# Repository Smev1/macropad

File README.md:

This is my Hack Club Hack Pad!

I am making this to learn about how to use KiCAD!

PCB Schematic:

CAD Assembled:

CAD Parts:

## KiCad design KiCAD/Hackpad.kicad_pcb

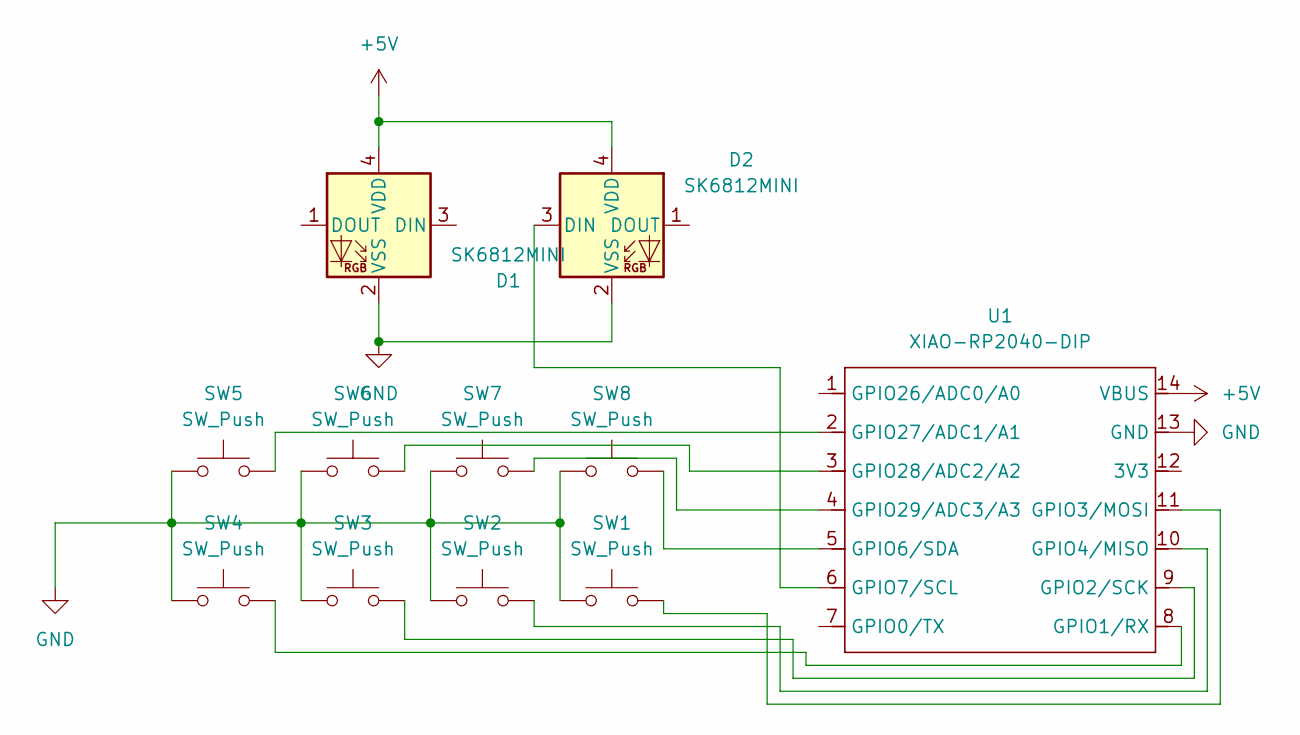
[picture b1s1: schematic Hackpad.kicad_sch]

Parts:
D1, D2: SK6812MINI; LED_SK6812MINI_PLCC4_3.5x3.5mm_P1.75mm
SW1, SW2, SW3, SW4, SW5, SW6, SW7, SW8: SW_Push; SW_Cherry_MX_1.00u_PCB
U1: XIAO-RP2040-DIP

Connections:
+5V: D1.4 (VDD), D2.4 (VDD), U1.14 (VBUS)
GND: D1.2 (VSS), D2.2 (VSS), SW1.1, SW2.1, SW3.1, SW4.1, SW5.1, SW6.1, SW7.1, SW8.1, U1.13 (GND)
unnamed: D2.3 (DIN), U1.6 (GPIO7/SCL)
unnamed: SW4.2, U1.8 (GPIO1/RX)
unnamed: SW3.2, U1.9 (GPIO2/SCK)
unnamed: SW1.2, U1.11 (GPIO3/MOSI)
unnamed: SW2.2, U1.10 (GPIO4/MISO)
unnamed: SW8.2, U1.5 (GPIO6/SDA)
unnamed: SW5.2, U1.2 (GPIO27/ADC1/A1)
unnamed: SW6.2, U1.3 (GPIO28/ADC2/A2)
unnamed: SW7.2, U1.4 (GPIO29/ADC3/A3)

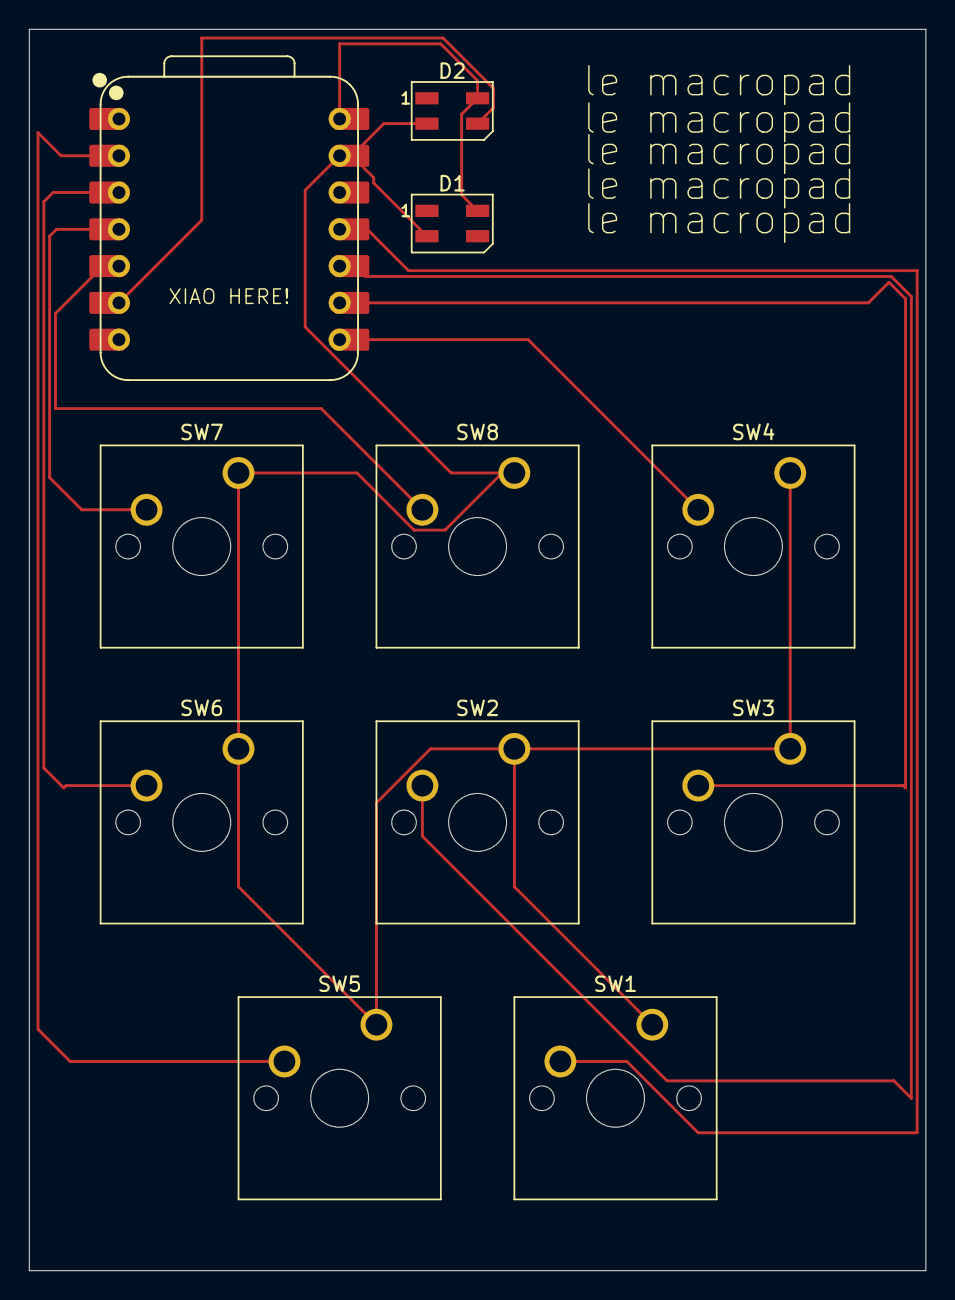
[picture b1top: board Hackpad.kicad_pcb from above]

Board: 2 copper layers, 61.9 x 85.7 mm, 11 parts (0 on the bottom side), 11 nets.

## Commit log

2026-01-17 Rename case.stl to CAD/case.stl
2026-01-17 Rename cover.stl to CAD/cover.stl
2026-01-17 Rename peg.stl to CAD/peg.stl
2026-01-18 Rename Hackpad.kicad_pro to KiCAD/Hackpad.kicad_pro
